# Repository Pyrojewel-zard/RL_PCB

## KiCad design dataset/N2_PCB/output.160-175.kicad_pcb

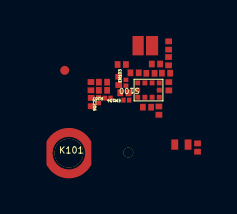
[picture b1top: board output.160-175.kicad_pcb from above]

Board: 2 copper layers, 26 parts (0 on the bottom side), 15 nets, no tracks yet.

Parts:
A118: INDUCTOR_IND0201-HT0_35_11NH; IND0201-HT0_35
A119: INDUCTOR_IND0201-HT0_35_5.6NH; IND0201-HT0_35
A122: INDUCTOR_IND0201-HT0_35_1NH; IND0201-HT0_35
A128: INDUCTOR_IND0201-HT0_42_3NH; IND0201-HT0_42
A129: CAP_NP_CAP0201-HT0_33_1.8PF; CAP0201-HT0_33
A130: CAP_NP_CAP0201-HT0_33_0.4PF; CAP0201-HT0_33
A131, A136, A145, A146: RES_RES0201-HT0_23_HD_0OHM; RES0201-HT0_23_HD
A133: INDUCTOR_IND0402CS-HT0_6_3.9NH; IND0402CS-HT0_6
A134, A135: CAP_NM_CAP0201-HT0_33_NM_NM; CAP0201-HT0_33_NM
C205: CAP_NP_CAP0201-HT0_33_33PF; CAP0201-HT0_33
C206: CAP_NP_CAP01005_HT0_22_S0_38_0.; CAP01005_HT0_22_S0_38
EM102: CAP_NP_CAP0201-HT0_33_100PF; CAP0201-HT0_33
EM103, EM104: CAP_NM_CAP01005_HT0_22_NM_NM; CAP01005_HT0_22_NM
J106: KEY_2P_ANT_1_0X1_7_P2_HT1_45_HD; ANT_1_0X1_7_P2_HT1_45_HD
K101: NUT_PAD-RING-TYPE-C_N2_PAD-RING; PAD-RING-TYPE-C_N2
L200: INDUCTOR_IND0201-HT0_35_180NH; IND0201-HT0_35
R205, R206: RES_RES0201-HT0_23_HD_0OHM; RES0201-HT0_23_HD
R207: RES_RES01005_HT0_15_S0_38_0OHM; RES01005_HT0_15_S0_38
S100: QM13145_SMT1_2X1_6_PS0_4-HT0_5_; SMT1_2X1_6_PS0_4-HT0_5_P10_HD
W201: SHORT_SHORT_RES0_06_HD_5_SHORT; SHORT_RES0_06_HD_5

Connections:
CDC_MIC4_N: C205.2, R206.2
CDC_MIC4_P: C205.1, R205.2
GND: A118.1, A119.1, A128.1, A133.2, A134.2, A135.2, C206.2, EM102.2, EM103.2, EM104.2, J106.1, J106.2, K101.1, R207.2, S100.7
N17753078: A122.1, A130.2, A131.1, A135.1
N17753084: A122.2, S100.1
N17753221: A119.2, S100.8
N17753329: A118.2, S100.2
N17753375: A128.2, S100.9
N17753406: A136.2, EM102.1, S100.3, S100.4
N17753412: A129.2, A130.1, A133.1, S100.10
N17753435: A145.2, EM103.1, S100.5
N17753447: A146.2, EM104.1, S100.6
N17753582: A131.2, A134.1
N17757493: R206.1, R207.1
WCD_MIC_BIAS4: C206.1, L200.1

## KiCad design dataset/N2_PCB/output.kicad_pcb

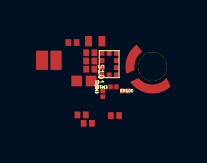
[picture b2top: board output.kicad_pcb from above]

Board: 2 copper layers, 15 parts (0 on the bottom side), 10 nets, no tracks yet.

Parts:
A107: INDUCTOR_IND0402CS-HT0_6_FPC_S_; IND0402CS-HT0_6_FPC_S
A108: CAP_NP_CAP0201-HT0_33_1.6PF; CAP0201-HT0_33
A109: CAP_NP_CAP0201-HT0_33_2.7PF; CAP0201-HT0_33
A110: INDUCTOR_IND0201-HT0_35_15NH; IND0201-HT0_35
A111: CAP_NP_CAP0201-HT0_33_33PF; CAP0201-HT0_33
A112: INDUCTOR_IND0402CS-HT0_6_10NH; IND0402CS-HT0_6
A141: RES_RES0201-HT0_23_HD_0OHM; RES0201-HT0_23_HD
A149: RES_RES0201-HT0_23_HD_10OHM; RES0201-HT0_23_HD
A150: CAP_NP_CAP0201-HT0_33_100NF; CAP0201-HT0_33
EM100, EM101: RES_NM_RES01005_HT0_15_S0_38_NM; RES01005_HT0_15_S0_38_NM
EM105: CAP_NM_CAP01005_HT0_22_NM_NM; CAP01005_HT0_22_NM
J102: KEY_2P_ANT_1_7X1_0_P2_HT1_35_HD; ANT_1_7X1_0_P2_HT1_35_HD
J112: ANT_PIN_ANT_HG_F1_XM-217-XC-186; ANT_HG_F1
S101: QM13344_SMT1_1X1_5_HT0_45_10P_H; SMT1_1X1_5_HT0_45_10P_HD

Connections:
GND: A112.2, A150.2, EM100.2, EM101.2, EM105.2, J112.1, S101.5, S101.10
N17753661: A149.2, A150.1, EM105.1, S101.3, S101.4
N17753743: A111.1, J102.1, J102.2
N17753749: A107.1, A108.1, A109.1, A110.1, A111.2, A112.1
N17753816: A109.2, S101.8
N17753880: A108.2, S101.7
N17753882: A141.1, EM100.1, S101.2
N17753954: EM101.1, S101.1
N17837242: A110.2, S101.6
N17837274: A107.2, S101.9

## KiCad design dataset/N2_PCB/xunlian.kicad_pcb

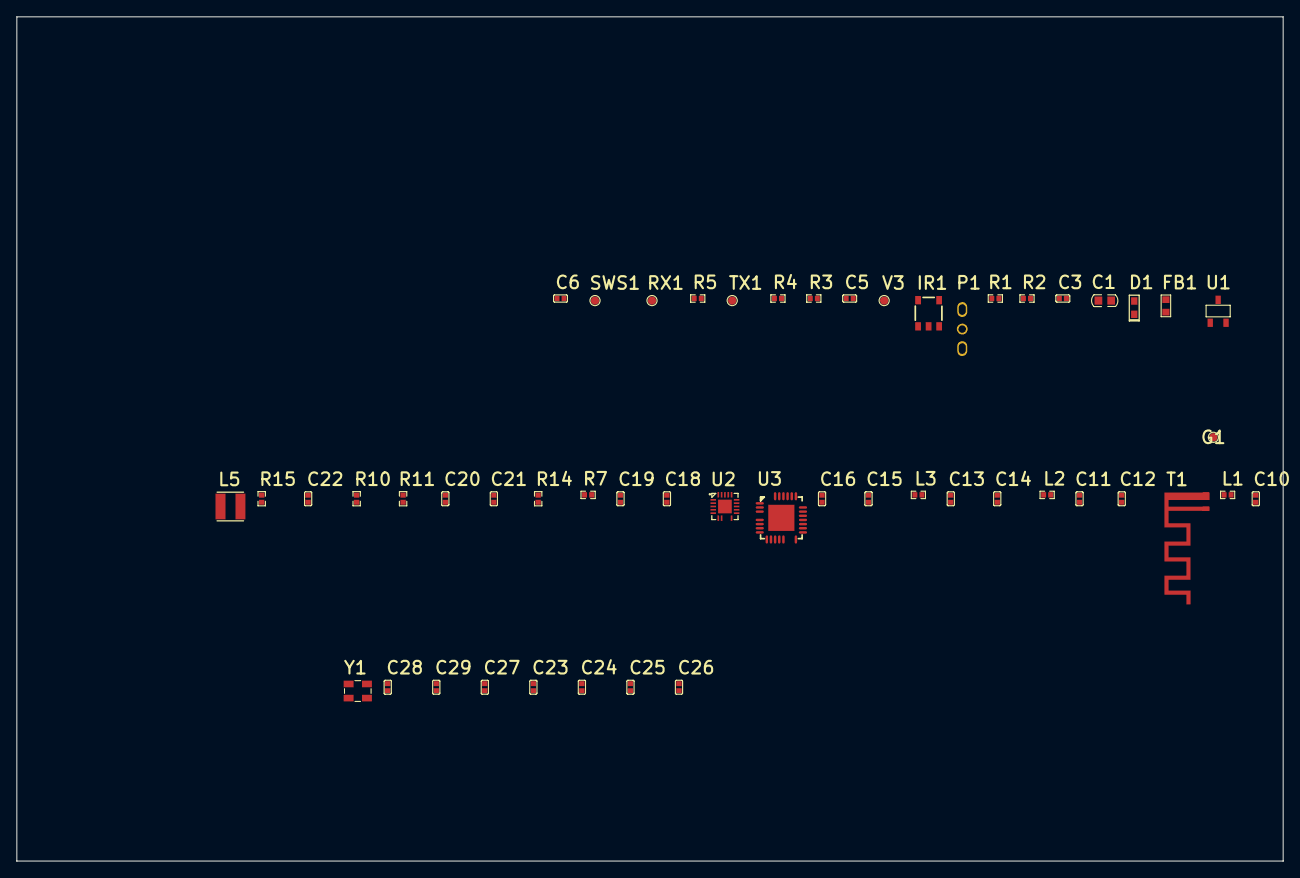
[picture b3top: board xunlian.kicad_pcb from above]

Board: 2 copper layers, 152.4 x 101.6 mm, 51 parts (0 on the bottom side), 39 nets, no tracks yet.

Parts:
C1: 10uF/16V; C0603
C3, C13, C21, C28: 10uF; C0402
C5, C14, C29: 100nF; C0402
C6: 10nF; C0402
C10: 220pF; C0402
C11: 2.2uF; C0402
C12, C16, C18, C22, C24, C25, C26, C27: 1uF; C0402
C15: 18pF; C0402
C19, C20: 1nF; C0402
C23: 33nF; C0402
D1: PT19-21C; LED0603
FB1: GZ1608; R0603
G1: GND; D
IR1: LF0038Q; SMT-IRM
L1: 0R; R0402
L2: NC/1.3nH; R0402
L3: 1nH; R0402
L5: 47uH; L3015
P1: 3P; 3P-2.54
R1, R5: 100R; R0402
R2: 39K; R0402
R3: 47k; R0402
R4, R11: 1K; R0402
R7, R14: 10k; R0402
R10, R15: 0; R0402
RX1: T; D
SWS1: RST; D
T1: TP; BLE_ANT_M
TX1: R; D
U1: LR8103A-T33; SOT23-3-L
U2: XBR818; QFN20_3x3
U3: TLSR8359F512ET32; QFN32
V3: 3V3; D
Y1: 32MHz; SMD3225

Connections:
1V2: C11.1, C12.1, C28.1, C29.1, U3.12, U3.28
3.3V: C3.1, C13.1, C14.2, C22.1, C26.1, D1.2, R1.2, R2.2, R14.1, U1.2, U2.18, U3.9, U3.18, U3.19, V3.1
5V: FB1.1, P1.3
AD: C23.1, R15.2, U3.6
CDS: C5.1, D1.1, R3.2, U3.16
GND: C1.2, C3.2, C5.2, C6.1, C11.2, C12.2, C13.2, C14.1, C15.2, C16.2, C18.2, C19.2, C21.2, C22.2, C23.2, C24.2, C25.2, C26.2, C27.2, C28.2, C29.2, G1.1, IR1.4, L3.2, P1.1, R3.1, R7.1, R10.1, U1.1, U2.5, U2.17, U2.21, U3.7, U3.33, Y1.2, Y1.4
I2C_SCL: U2.12, U3.21
I2C_SDA: U2.11, U3.20
IR: C6.2, R5.1, U3.23
MCU-OUT: R4.1, U3.1
NetC1_1: C1.1, FB1.2, U1.3
NetC10_1: C10.1, L2.2, U3.27
NetC10_2: C10.2, L1.1
NetC15_1: C15.1, L2.1, U3.26
NetC18_1: C18.1, U2.3
NetC19_1: C19.1, U2.2
NetC20_1: C20.1, R15.1, U2.20
NetC20_2: C20.2, R11.2, U2.1
NetC21_1: C21.1, R11.1
NetC24_1: C24.1, U2.19
NetC25_1: C25.1, U3.8
NetC27_1: C27.1, U3.13
NetIR1_3: IR1.3, R2.1, R5.2
NetIR1_5: IR1.5, R1.1
NetL1_2: L1.2, T1.1
NetL5_1: L5.1, U3.11
NetL5_2: L5.2, U3.10
NetR7_2: R7.2, U2.14
NetR14_2: R14.2, U2.13
NetU2_15: U2.15, U2.16
O: P1.2, R4.2
RF_TX: L3.1, U2.6
RST: C16.1, U3.25
RX: RX1.1, U3.3
SWS: SWS1.1, U3.5
TX: TX1.1, U3.2
VRE: R10.2, U3.22
XTAL1: U3.29, Y1.3
XTAL2: U3.30, Y1.1

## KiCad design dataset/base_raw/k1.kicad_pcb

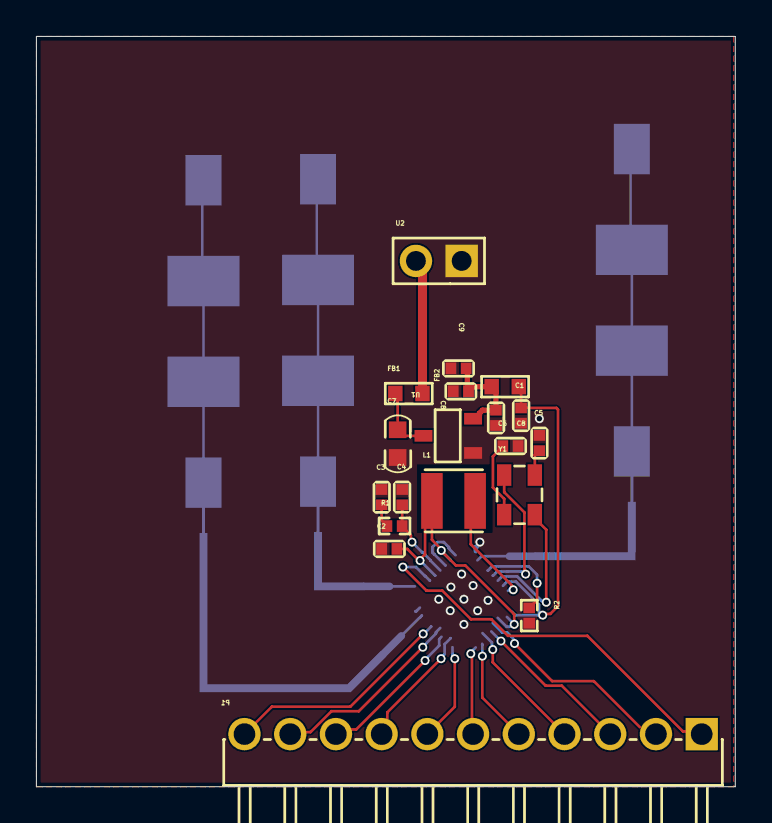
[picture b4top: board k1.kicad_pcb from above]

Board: 2 copper layers, 38.8 x 41.7 mm, 20 parts (1 on the bottom side), 26 nets.

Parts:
C1, C9: 100nF; C0402
C2: 22uF; C0402
C3: 4.7nF; C0402
C4: 820pF; C0402
C5: 12pF; C0402
C6: 120pF; C0402
C7: 10uF; C0603
C8, C8#2: 10uF; C0402
FB1, FB2: GZ1608; R0603
L1: 22uH; L3015
P1: header_11; HEADER_11
R1: 820; R0402
R2: 12K; R0402
U1: LR8103A-T33; SOT23-3-L
U2: P2; HX PZ2.54-1x2P ZZ
U3: ICL1122; ICL2211
Y1: 25MHz; SMD3225

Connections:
3.3V: C8.2, C8#2.2, C9.2, FB2.2, U1.2
5V: FB1.1, U2.2
DCDC_SW: L1.1, U3.16
GND: C1.1, C2.2, C3.2, C4.1, C5.2, C6.1, C7.1, C8.1, C8#2.1, C9.1, R2.1, U1.1, U2.1, U3.2, U3.9, U3.11, U3.30, U3.32, U3.33
I2C_SCL: P1.3, U3.21
I2C_SDA: P1.2, U3.20
NetC2_1: C2.1, L1.2, U3.4, U3.7, U3.18, U3.19
NetC3_1: C3.1, R1.2
NetC5_1: C5.1, Y1.2
NetC6_2: C6.2, Y1.4
NetC7_2: C7.2, FB1.2, U1.3
NetU3_6: U3.6, U3.8
PLL_VC: C4.2, R1.1, U3.5
RAW-CLK: P1.6, U3.24
REXT: R2.2, U3.12
RSTN: P1.1, U3.3
SPI_CSN: P1.8, U3.26
SPI_DO_0: P1.9, U3.27
SPI_DO_1: P1.10, U3.28
SPI_SCLK: P1.11, U3.29
SYNC_IN: P1.4, U3.22
SYNC_OUT: P1.5, U3.23
UART_TXD: P1.7, U3.25
VDD: C1.2, FB2.1, U3.15, U3.17
XIN: U3.14, Y1.1
XOUT: U3.13, Y1.3
